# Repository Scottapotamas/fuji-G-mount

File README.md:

# Fujifilm G Mount
The Fujifilm G Mount is used by the Fujifilm GFX line of digital medium format mirrorless cameras.

Since the announcement in 2016, the GF lens ecosystem has been gaining popularity due to the superb optical performance, high megapixel camera bodies (GFX100), and low cost (well... compared to other MFD systems).

One minor challenge compared to most existing lens ecosystems - **all GF lenses are fly-by-wire**. Sensing user interaction with the aperture or focus rings, and commanding the iris and focus mechanisms will require computer control. Additionally, lenses such as the 110mm f2 and 250mm f4 have floating optical elements which require power/control from the body in order to become optically valid.

____

My long-term photography/hobby goals are rather ambitious; *build a film camera from scratch using modern lenses*. A 120 'body' for my GF lenses feels like the right kind of wrong...

## Aims

- [x] Document the mechanics of the G Mount sufficiently to create native-compatible mounts from scratch.
- Reverse-engineer & document the communications between the lens and body:
  - [x] Pinout for the electrical contacts in the lens mount,
  - [ ] Power supply requirements for lenses,
  - [x] Sniff the communications between the lens and camera, and document any specifics if possible.
- [ ] Write a library capable of parsing lens data (in both directions) in real-time.
- [x] Create an interface PCB which pretends to be a GFX camera - powers and controls an attached lens, can read lens info and focus/iris ring feedback.

## Prior Art?

At time of writing, no publicly available information about the mount's mechanics could be found other than the flange distance and internal diameter.

Similarly, any electrical interface or protocol information is not in the public domain.

> There's a good chance the Fuji X-mount uses a similar protocol or structure. Couldn't find any information for that either...

Several active (3rd party) lens adaptors *are* on the market, allowing smart control over Canon EF, Contax C645, and others. Therefore we can guess at least three different groups have successful implementations with varying levels of functionality.

## What's the plan

- [x] Buy a genuine Fujifilm extension tube [MCEX-45G WR](https://fujifilm-x.com/global/products/accessories/mcex-45g-wr/) to act as a ground-truth mechanical mount.
   - The absurd $500AUD pricepoint is painful, but won't risk my camera or lenses. I managed to get 25% off MSRP.
   - I could use one of the $150AUD Viltrox clone extension tubes later on, but I want an accurate first-party reference to build against.
- [x] Create detailed 3D models of the male and female mount geometries, identify screws/springs/gaskets used. Refer [`/mechanical`](/mechanical).
- [x] Dissemble the extension tube, design a replacement 'cylinder' to mount the genuine mounting faces onto. Or just seal it's fate and drill a hole in the adaptor...
   - Expose the lens and body electrical contacts through a loom or connector - ideally each side can be separated at will for easier debugging.
- [x] Map the electrical connections between the body and lens, create rough specs for power rails, determine the style of communication and electrical implementation(s) in use. Refer [`/electrical`](/electrical).
- [x] Assuming no strange electrical interfaces are used, connect the logic analyser/scope and build out a corpus of messages sent between the lens and body.
  - Refer [`/protocol`](/protocol) for notes.
  - Capture control ring, iris closure, focus motor on GF110 to compare against 45mm findings.
- [ ] Write a basic library implementation with unit tests against captured packets
   - [ ] Connect a micro running the library in real-time to the body, see what works/doesn't.
   - [ ] Connect micro to lens, see if setting iris or focus is possible

## What have we learnt

- Enough to successfully make a [GF mount adapter for the Fuji MK series S35 cine-zooms](https://github.com/Scottapotamas/fuji-mk-zoom-to-GF-mount).
- Protocol behaviour for a subset of packets: 
  - Aperture index and relative focus ring rotations sent from the lens to the camera
  - Closing the iris
  - Commanding absolute focus motor position
  - Some hazy details on the packet shapes

# References & Acknoledgements

- A [large mirror of firmware updates](https://u.pcloud.link/publink/show?code=kZRGzJXZA5zjOTgVm2FJjdvTIG1UekBLWefV#/filemanager?folder=7261419858) here by [Manzur Fahim on DPreview](https://www.dpreview.com/forums/threads/fujifilm-gf-lens-firmware-not-available-anymore.4824834/post-68549141).

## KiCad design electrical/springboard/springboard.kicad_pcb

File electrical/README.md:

# GF Mount Electrical Notes

[`springboard`](./springboard) contains PCB design files for a pogo-pin based breakout used to electrically interface with a lens.

General documentation below.

# Basics

The electrical connections between the body and lens are made with 12 spring loaded contacts (body) which mechanically align with 11 contact rectangles (lens).

## Body Side

- Spring-loaded pins are on the body side, flat pads are on the lens side.
- The spring section of the pins have a 1.0 mm diameter, and a maximum achievable travel of 0.8mm.
- The spring pins have a conical/round tip.
- The pins are gold.
- The pins are spaced 6° apart, for a total span/range of 66°. There is no pin on the vertical from the mount center-point, the outermost edge pins are aligned at +33° and -33° from the vertical datum.
- The mount (metal ring/bayonet assembly) is electrically common with the exposed metal inside the battery compartment, and `Pin 5` and `Pin 6`.

## Lens Side

- The lens-side contacts are 1.6 x 1.3 mm rectangular pads, with the long edge aligned tangentially to the circular mount.

- When looking at the back of the lens mount, the right-most pin is a 1.3 mm x 1.3 mm square contact.

- For ease of convention, I'll label this square pad as `Pin 1`, though I don't know what the official Fuji nomenclature is.

- Based on this numbering scheme, `Pin 5` and `Pin 6` are mechanically the same contact rectangle, and therefore electrically common.

- Unlike the body side mount, the lens mount/bayonet is not electrically common with `Pin 5` and `Pin 6`.

# Poking the MCEX-45G

The extension tube provides probable contacts for both sides of the mount.

Flange to flange conductivity doesn't seem to be something that's explicitly designed for, most mating surfaces on the extension tube are anodised (therefore not conductive by contact), so the electrical path is likely through the mounting screws.

The camera-side electrical connections are larger through-hole style slugs which are soldered to the flex PCB and covered with some high quality kapton tape.

The lens-side pins are more complicated. The spring contacts are actually a bespoke assembly that Fuji has designed, they don't use COTS style pogo-pins. 

- Small copper or gold (plated?) pins slide in the plastic ring.
- The flex PCB has circular exposed pads on fingers which contact the back of the gold pins. 
- An injection molded plastic retainer contains individual springs for each contact (12 in total).
- I'd recommend strongly avoiding pulling this sub-assembly apart. There are no features to retain or guide the springs, instead, the plastic retainer has 12 tiny holes presumably used with a jig during factory assembly. I had to make my own jig with needles.

After inspecting the flex PCB,  we can assume the substantially thicker traces are used on Pins 2 through 6 are used for power delivery and grounding.

- The extension tube's electrical connections are a straight 1:1 passthrough,

- therefore, the camera cannot distinguish if the tube is attached.

- Electrical connections appear to be direct connections - measurements below are subject to  measurement error.

  | Pin-Pin           | Resistance (Ω) |
  | ----------------- | -------------- |
  | Flange            | 0.14           |
  | 1 (square)        | 0.32           |
  | 2                 | 0.08           |
  | 3                 | 0.13           |
  | 4                 | 0.12           |
  | 5 (joined with 6) | 0.05           |
  | 6 (joined with 5) | 0.08           |
  | 7                 | 0.23           |
  | 8                 | 0.20           |
  | 9                 | 0.25           |
  | 10                | 0.28           |
  | 11                | 0.27           |
  | 12                | 0.29           |

The extension tube was reassembled and tested working without issue. Assembly is mostly uneventful if the lens side contact springs are left alone. The whole process took about 3-4 hours.

# Modifying the MCEX-45G for interactive instrumentation

After dissasembly (again), the external ring and internal column were taped up to avoid scratches, and marked for a drilled hole.

A 1.0mm pilot hole was drilled, followed by a 4.5mm bore. This was repeated for both cylindrical pieces. The holes were then de-burred and tape removed.

The kapton tape protecting the through-hole pins from the body-side contacts was removed.

Silicone flying leads were soldered to the back of the flex.

Fresh kapton tape was applied to protect the solder joins from electrical contact with the tube/mount.

After full assembly, the assembly was tested with the camera/lens to ensure no loss of operation.

The flying leads were crimped for a female 2.54mm header strip.

This process took about 2-3 hours.

# Electrical Behaviour

Oscilloscope traces and logic-analyser capture to give context to the basic behaviour.

- All tests use the GFX50R and GF45mm with MCEX-45G.
- The camera has shutter-speed set to 1/125th, ISO 100, normally F4, 
- The camera was running from the internal battery only.
- Grounding for the scope/logic analyser is through Pins 5 and 6 respectively.

The LA capture below shows a simple sequence covering power on, focus, focus+photo, power off.

Pin names are listed in the left-hand column, and the timing markers along the top timeline have annotations matching their number/colour in the right-hand sidebar.

## Test Description

Voltage measurements taken with Keithley 2701 (front panel, 2 wire setup).

Scope set to rising/falling trigger at 100mV, 1V/div and 5ms/div.

Each pin was tested with the camera off, then turned on, autofocus engaged, then camera was turned off.

The ground was assumed to be Pin 5 based on:

- Higher current traces in MCEX-45G.
- Common with Pin 6 on lens mount side.
- Electrically common (v.low resistance to Pin 6 and GFX body-side mount).

### No lens connected

GFX 50R with MCEX-45G. No lens mounted.

| Pin  | Voltage  | Scope/Notes                                                  |
| ---- | -------- | ------------------------------------------------------------ |
| 1    | 3.3V     | Goes high when camera turned on, slow fall when camera turned off. |
| 2    | ~10mV    | -                                                            |
| 3    | ~10mV    | -                                                            |
| 4    | ~0.003mV | -                                                            |
| 5    | -        | Used as ground connection.                                   |
| 6    | 0mV      | Electrically common to Pin 5.                                |
| 7    | 8mV      | -                                                            |
| 8    | 8mV      | -                                                            |
| 9    | 8mV      | -                                                            |
| 10   | 7mV      | -                                                            |
| 11   | 8mV      | -                                                            |
| 12   | 15mV     | -                                                            |

### GF45mm connected

GFX 50R with GF 45mm f2.8 via MCEX-45G.

| Pin  | Voltage |               | Scope/Notes                                                  |
| ---- | ------- | ------------- | ------------------------------------------------------------ |
| 1    | 0V      |               | Never triggers scope, even with varied settings.<br />Acting as (part of) lens detect? |
| 2    | 5.32V   |               | Just DC.                                                     |
| 3    | 6.72V   |               | Just DC.                                                     |
| 4    | 8.01V   |               | Just DC.<br />Minor ~100mV ripple when focus motor engages.  |
| 5    | -       | -             | Used as ground connection for scope                          |
| 6    | -       | -             | Electrically common to Pin 5                                 |
| 7    | 3.4V    | Normally high | Infrequent squarewave behaviour.<br />No immediately recognisable pattern. |
| 8    | 3.38V   | Normally high | High speed edges, infrequently triggered.<br />Pulses LOW for approx 100-350ns at a 10ms interval. |
| 9    | 0V      | Normally low  | Squarewave, role unclear but probably data line.             |
| 10   | 3.3V    | Normally high | Squarewave, obviously a clock line at 1.5MHz.<br />Used periodically. |
| 11   | 0V      | Normally low  | Squarewave, obvious data line.                               |
| 12   | 3.3V    | Normally high | Squarewave, no discernable pattern.<br />Seems to go low when iris closes. |

## Pin 7

- Trace is captured after the camera was asked to focus on an object. 
- Logic level. Normally high.
- No obvious pattern, but is mostly likely related to AF lens motor activation.

## Pin 10

- 1.5Mhz squarewave on Pin 10.
- Logic level. Normally high.
- Is assumed to be a SPI style clock. 

## Pin 11

- Pin 11 appears to behave like a SPI style data line. 
- Logic level. Normally low. 

## Pin 12

- Iris ring on lens is being twisted slowly by hand.
- Logic level. Normally high.
- Correlates to iris inside the lens closing. The short flickers in this trace anecdotally match the sound of the iris, and the exposure-flicker behaviour of the EVF as the camera adjusts.

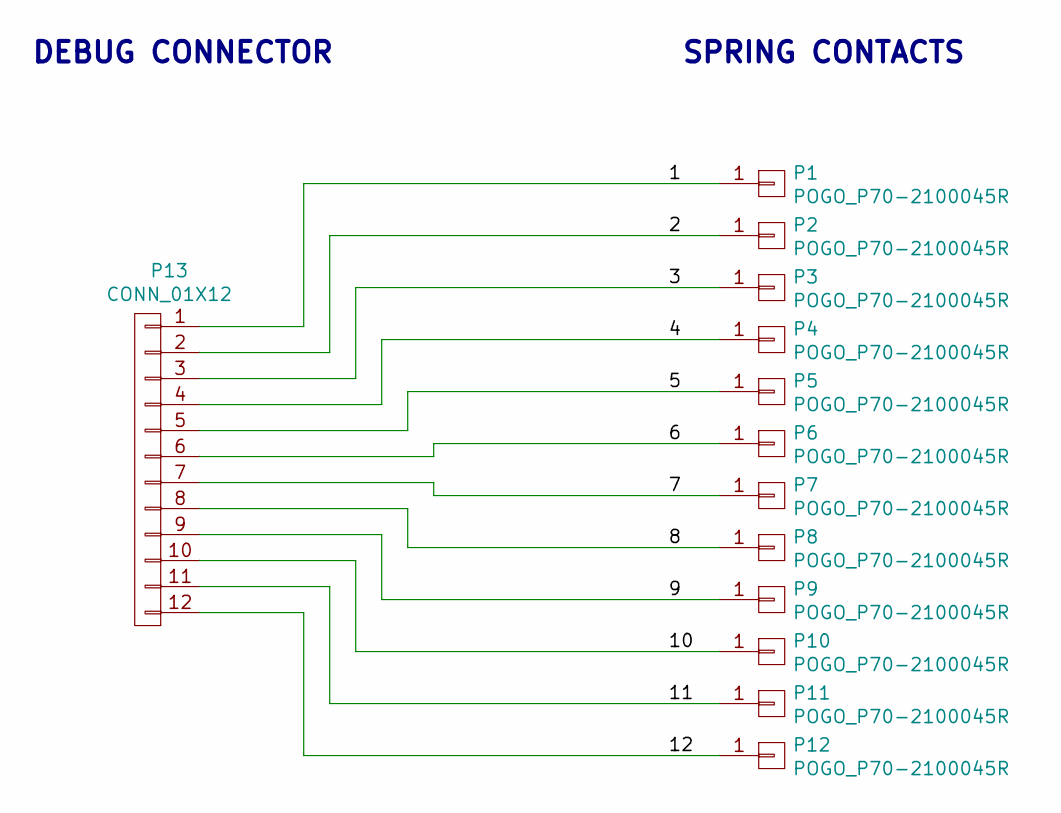
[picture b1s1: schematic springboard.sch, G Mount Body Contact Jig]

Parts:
P1, P2, P3, P4, P5, P6, P7, P8, P9, P10, P11, P12: POGO_P70-2100045R; HARWIN_P70-2100045R
P13: CONN_01X12; 61301211121

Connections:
/1: P1.1, P13.1
/2: P2.1, P13.2
/3: P3.1, P13.3
/4: P4.1, P13.4
/5: P5.1, P13.5
/6: P6.1, P13.6
/7: P7.1, P13.7
/8: P8.1, P13.8
/9: P9.1, P13.9
/10: P10.1, P13.10
/11: P11.1, P13.11
/12: P12.1, P13.12

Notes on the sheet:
SPRING CONTACTS
DEBUG CONNECTOR

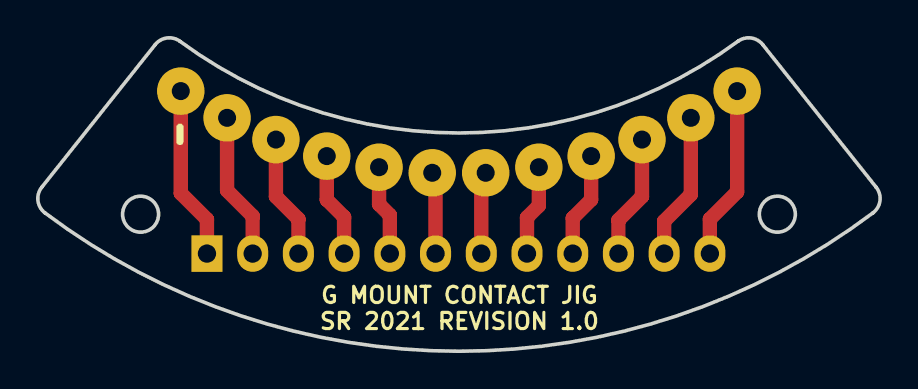
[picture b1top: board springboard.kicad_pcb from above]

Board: 2 copper layers, 46.8 x 17.4 mm, 13 parts (1 on the bottom side), 12 nets.

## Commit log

2021-02-15 Condensed preliminary thoughts in README
2021-02-15 Added rest of README thoughts
2021-03-04 Started adding notes about GF mount contacts
2021-03-04 Prelim CAD reference drawings of pins and pads in GF mount
2021-03-04 Prelim reference drawing for GF lens electrical contacts
2021-03-05 Folder structure stubs
2021-03-06 DXF export for pin test PCB
2021-03-07 Quick PCB to mount spring-contacts matching G-mount body side
2021-03-07 Spring-contact PCB gerbers, renders, PDF exports
2021-03-10 Note about body/lens mount metal electrical continuity
2021-08-15 Resistance measurements of GF extension tube
2021-08-21 Add basic images of MCEX-45G extension tube
2021-09-18 CAD model of lens-side of mount
    Measured carefully and validated with scans of front and back faces.
2021-09-18 CAD model of body-side of mount
    Measured carefully and validated with scans of front and back faces.
2021-09-18 Added lens mount rotation stop 'square' piece
    Prevents lens barrel from rotating past the lock position
2021-09-18 Added body-mount spring shim part
    Provides preload against lens mount
2021-09-18 Physics based motion test of mount/unmount lens from body piece
    Tolerances seem to be ok, clearance tests pass
2021-09-19 Notes on electrical analysis
2021-09-20 Electrical notes with images of tube modification and trace captures
2021-09-20 Improvements to electrical and MCEX tube modification
    Added images and descriptions of teardown for context.
2021-09-20 Add SPI notes and some preliminary packet analysis
    Lens identification and body identification packets identified.
2021-09-20 Add logic analyser save files, and packet binary files to source control
2021-09-20 Minor docs update in electrical README
2021-09-20 Adds renders of body and lens mount flanges
2021-09-21 Started mechanical README, folder reorganisation.
2021-09-21 Additional protocol notes as decoding attempts continue
2021-09-26 Setup ceedling test environment for 'CRC' evaluations
2021-09-27 Added lens/body identification packets to checksum unit tests
2021-10-30 Commit missed CRC unit test stubs
2026-05-21 Some readme cleanup
2026-05-21 Add captures of isolated iris closures to build out reference library
2026-05-21 Findings on lens control ring packets, 'actuate iris' command
2026-05-22 Focus ring packet captures and analysis notes/plots
2026-05-22 Focus motor packet captures
2026-05-22 Focus motor command/feedback analysis notes/plots
2026-05-23 wip notes on packet structure and checksum byte?
2026-05-23 Add GF110 packet captures, notes, some small thoughts in protocol/etc
2026-05-23 Notes from first pass over GF110 captures, more iris captures
2026-05-23 Notes on aperture command packet sequence/encoding
2026-05-23 Notes on command ack flag
2026-05-24 Continued final byte analysis, 'novel' packets for stubbed analysis notes
2026-05-25 Protocol notes, stubs for OIS/zoom/teleconverter/shift-rotation sensor
2026-05-25 Protocol notes cleanup
2026-05-25 Protocol cleanup for iris feedback, focus command sequencing
2026-05-25 Add novel commands found in older GF captures Should have included power up/down and more focus behaviours in the recent series of captures...
2026-05-25 Add GF110 and GF45 additional captures
2026-05-25 Protocol notes on 5-bit checksum algo
2026-05-26 Remove old CRC unit test stubs, protocol notes updates, lens ident strings
2026-05-26 Capture of GF110 running firmware update
2026-05-27 Continued protocol notes cleanup/re-arrange order
2026-05-30 Continued protocol cleanup, periodic status polling
2026-06-29 Hanging docs commit
